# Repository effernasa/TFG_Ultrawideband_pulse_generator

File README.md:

View this project on [CADLAB.io](https://cadlab.io/project/30454). 

# TFG_Ultrawideband_pulse_generator

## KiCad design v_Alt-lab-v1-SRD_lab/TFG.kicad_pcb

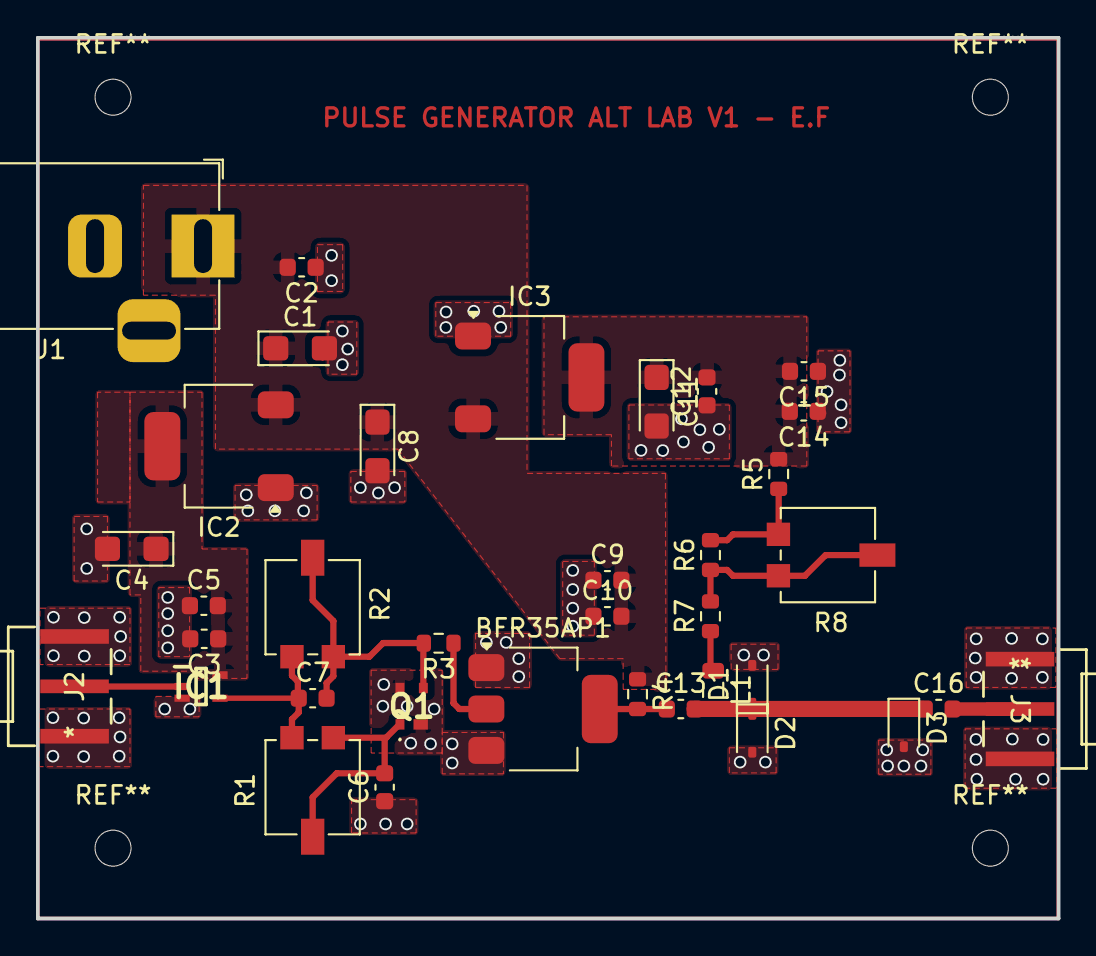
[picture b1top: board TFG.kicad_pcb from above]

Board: 2 copper layers, 56.7 x 48.9 mm, 36 parts (0 on the bottom side), 15 nets.

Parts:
BFR35AP1: Q_NPN_BCE; SOT-223-3_TabPin2
C1, C4, C8, C11: 10u; CP_EIA-3216-18_Kemet-A
C2, C3, C6, C7, C9, C10, C13, C14, C15, C16: C; C_0603_1608Metric
C5, C12: 0.1u; C_0603_1608Metric
D1, D2: SMS3923-079LF; D_SOD-323
D3: SRD_MA144769-287T; D_SOD-323
IC1: MC74VHC1GT04DFT2G; SOT65P210X110-5N
IC2, IC3: TS1117BCW50 RPG; SOT-223-3_TabPin2
J1: Jack-DC; BarrelJack_Horizontal
J2, J3: CON-SMA-EDGE-SRP; CON-SMA-EDGE-SRP_RFS
L1: L; L_0805_2012Metric
Q1: BFP420
R1, R2, R8: R_Variable; Potentiometer_Vishay_TS53YL_Vertical
R3: 0; R_0603_1608Metric
R4: R; R_0603_1608Metric
R5: 220; R_0603_1608Metric
R6: 330; R_0603_1608Metric
R7: 100; R_0603_1608Metric

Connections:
/I_bias: L1.1, R7.1
/V3v_in: IC1.2 (A), J2.1
/V5v: C3.1, C4.1, C5.2, IC1.5 (VCC), IC2.2 (VO)
/V5v_bias: C11.1, C12.2, C14.2, C15.2, IC3.2 (VO), R5.2
/V12v: C1.1, C2.2, C8.1, C9.2, C10.2, IC2.3 (VI), IC3.3 (VI), J1.1, R4.1
/Vout: C16.2, J3.1
/Vout_Driver: BFR35AP1.2, C13.1, R4.2
GND: BFR35AP1.3 (E), C1.2, C2.1, C3.2, C4.2, C5.1, C6.1, C8.2, C9.1, C10.1, C11.2, C12.1, C14.1, C15.1, D1.2 (A), D2.2 (A), D3.2 (K), IC1.3 (GND), IC2.1 (GND), IC3.1 (GND), J1.2, J1.3, J2.2, J2.3, J3.2, J3.3, Q1.2 (E_1), Q1.4 (E_2)
unnamed: BFR35AP1.1 (B), R3.1
unnamed: C13.2, C16.1, D1.1 (K), D2.1 (K), D3.1 (A), L1.2
unnamed: C7.1, IC1.4 (Y), R1.1, R2.1
unnamed: C6.2, Q1.1 (B), R1.2, R1.3
unnamed: C7.2, Q1.3 (C), R2.2, R2.3, R3.2
unnamed: R5.1, R6.2, R8.1
unnamed: R6.1, R7.2, R8.2, R8.3
